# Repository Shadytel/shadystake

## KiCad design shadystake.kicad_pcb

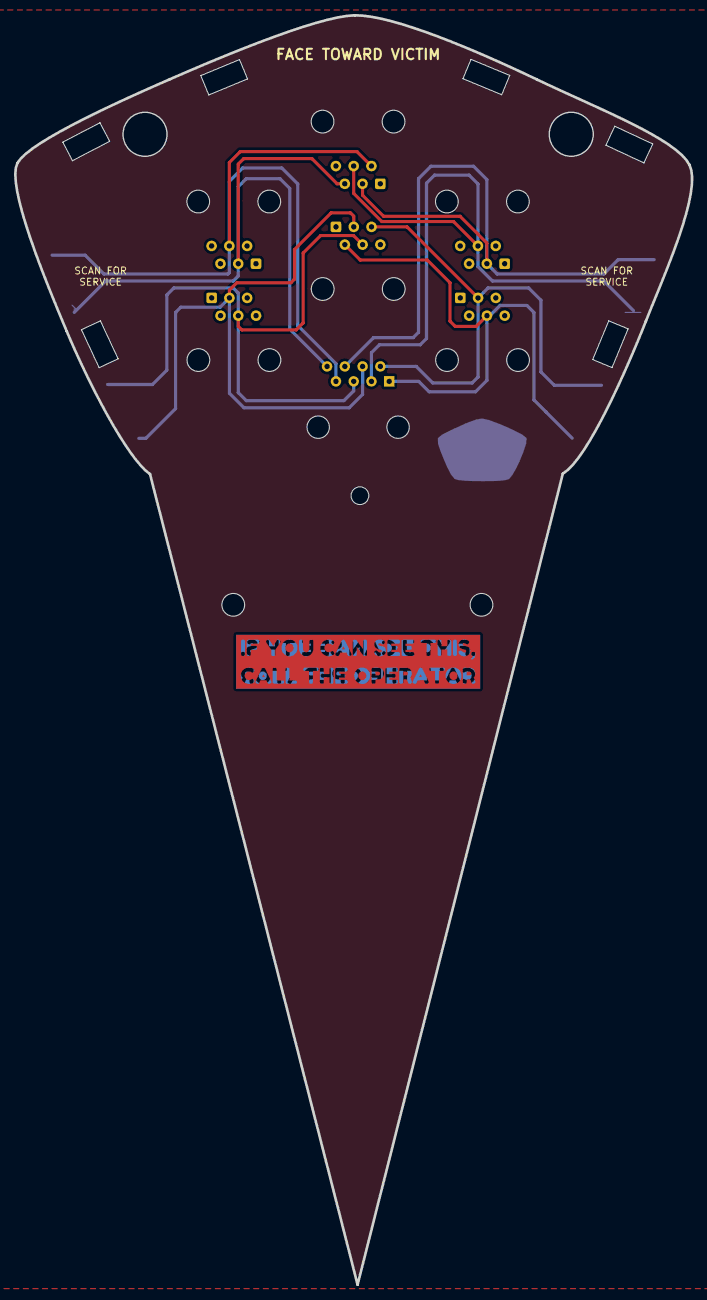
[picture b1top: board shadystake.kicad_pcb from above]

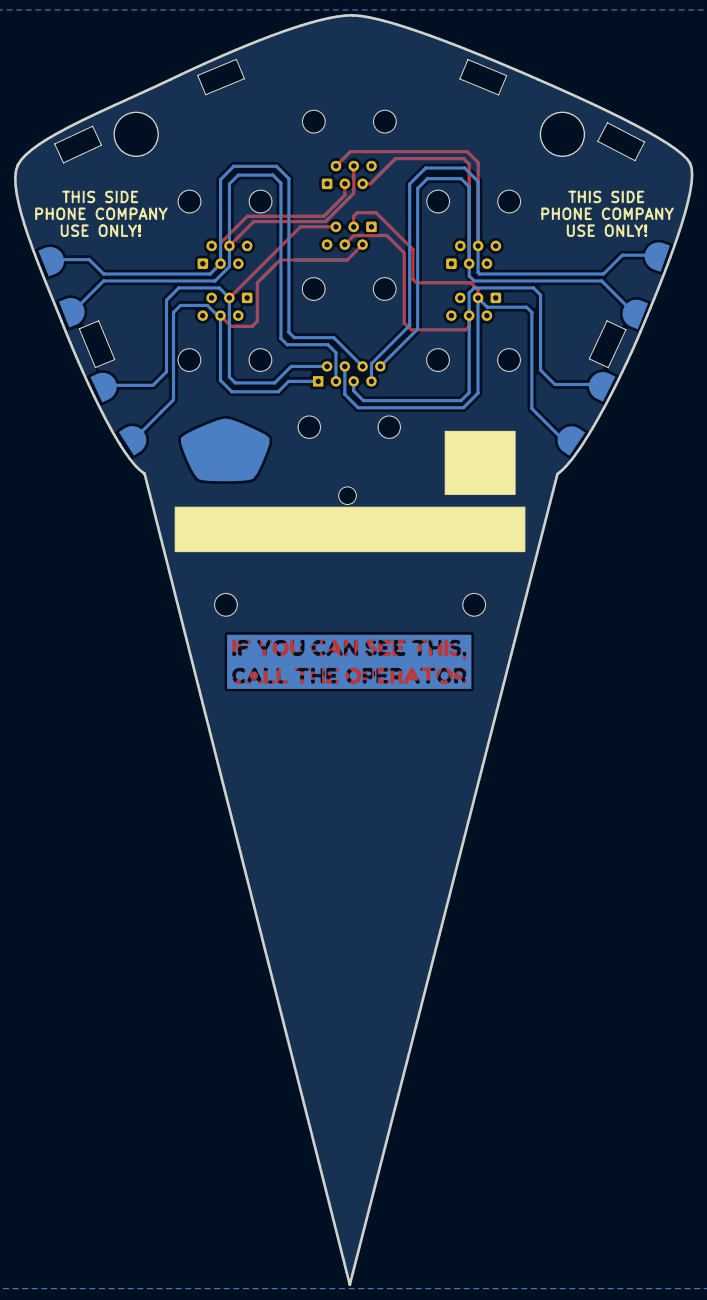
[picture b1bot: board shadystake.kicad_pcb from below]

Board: 2 copper layers, 96.8 x 181.5 mm, 25 parts (14 on the bottom side), 8 nets.

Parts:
J1, J2, J3, J4, J5, J6: 6P6C; RJ12_Amphenol_54601-x06_Horizontal
J7: 8P8C; 8P8C_Hor
TP1, TP2, TP3, TP4, TP5, TP6, TP7, TP8: TestPoint; TP
kibuzzard-62B55205, kibuzzard-62B55205#2: G***; kibuzzard-62B55205
svg2mod, svg2mod#4: G***; Steak_QR
svg2mod#2: G***; ground
svg2mod#3: G***; shadytel
svg2mod#5, svg2mod#6: G***; shock_warning
svg2mod#7: G***; shadytel_labs
svgemod: G***; ground

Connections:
/RING1: J1.3, J5.3, J7.4, TP2.1
/RING2: J2.3, J5.5, J7.2, TP4.1
/RING3: J3.3, J6.3, J7.6, TP6.1
/RING4: J4.3, J6.5, J7.8, TP8.1
/TIP1: J1.4, J5.4, J7.5, TP1.1
/TIP2: J2.4, J5.2, J7.1, TP3.1
/TIP3: J3.4, J6.4, J7.3, TP5.1
/TIP4: J4.4, J6.2, J7.7, TP7.1

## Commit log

2022-05-08 really rough draft of physical layout
    ⚠ spark gap footprints still completely missing
    modular jack footprints assumed to be the Amphenol SKU.
    The Board.Cuts shape still seems like awkward proportions, but in a
    manufacturable size.
2022-05-12 footprint: add library with simple spark gap
2022-05-13 footprint: add copper-fill keep-out to spark gap
2022-05-13 shadystake: make it roughly the proportions of the Shadytel logo
2022-05-13 pcb: add copper labels on the "wrong" side of the board
2022-05-14 first production run gerbers
2022-05-14 Gerber export settings and one minor reroute.
2022-05-26 Fix pin connections on several jacks and add more spark gaps
2022-05-28 fix spark gaps, continuity on PCB
2022-05-30 pcb: edit some routing, and add silkscreening on the back
2022-05-30 sparkgap: tweak keep-out a bit
2022-05-31 update footprints to have less silkscreening
2022-05-31 nudge stitching vias for aesthetic reasons
2022-05-31 Lay out design
2022-05-31 second run manufacturing artifacts
2022-05-31 Update edge cuts to make it a stake
2022-05-31 Update design and add footprints
2022-06-12 Rotate upper ports by 180 degrees to be compatible with side-insertion jacks
2022-06-12 WTF just happened
    Spark gaps are no longer connected to the ground place
2022-06-13 DRC 0
2022-06-26 Add QR code, Shadytel logo, and "call operator" note
2022-06-26 Add shadytel labs logo and "scan for service"
2022-06-26 More updates
2024-05-20 Update test point footprints
2024-05-23 Test point footprint hack, backported from KiCad 8
2024-05-23 TP footprint update
2024-05-23 TP fine adjustment
2024-05-23 DRC zero again
2025-09-14 Add raw QR code SVGs
2025-09-24 Add old QR code SVGs for reference
2025-09-29 F.Mask filled in
2025-09-29 Resized steak emoji
2025-10-04 Move missing rectangle to F.Mask layer and set stroke width to 0
2026-06-07 Remove circuit protection
2026-06-08 Update to KiCAD 10 and remove circuit protection
2026-06-08 Update QR code?
2026-06-08 Add QR code SVG exporter
2026-06-08 Add new QR code files
2026-06-08 Add default JLCPCB design rules file
2026-06-11 Reimport edge.cuts... jfc...
2026-06-11 Add silkscreen barcode area and RJ45 eject hole
2026-06-11 Add 2D barcode region
2026-06-11 Add enclosure holes
2026-06-11 Add port numbers
2026-06-11 Misc changes
2026-06-11 V3 manufacturing files
